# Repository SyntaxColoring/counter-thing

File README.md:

# Introduction

The Counter Thing is a hardware device with a button and numeric display. It currently counts days going up, and resets to 0 when you press the button.

I should run ~1 year on a CR2032 battery and keep time with a drift of <15 minutes/year.

I use a few as household reminders, like keeping track of how many days it's been since I've last vacuumed or watered my plants.

This repository holds everything for the project (electronics and software).

# File organization

[pcb/](./pcb/) has the KiCad project files for the latest version of the board. [pcb/fabrication_outputs/](./pcb/fabrication_outputs) has pre-exported Gerbers and such, ready to send to a fab. I used JLCPCB, but any of them will probably work.

[firmware/](./firmware/) has the STM32CubeIDE project files and source code for the firmware.

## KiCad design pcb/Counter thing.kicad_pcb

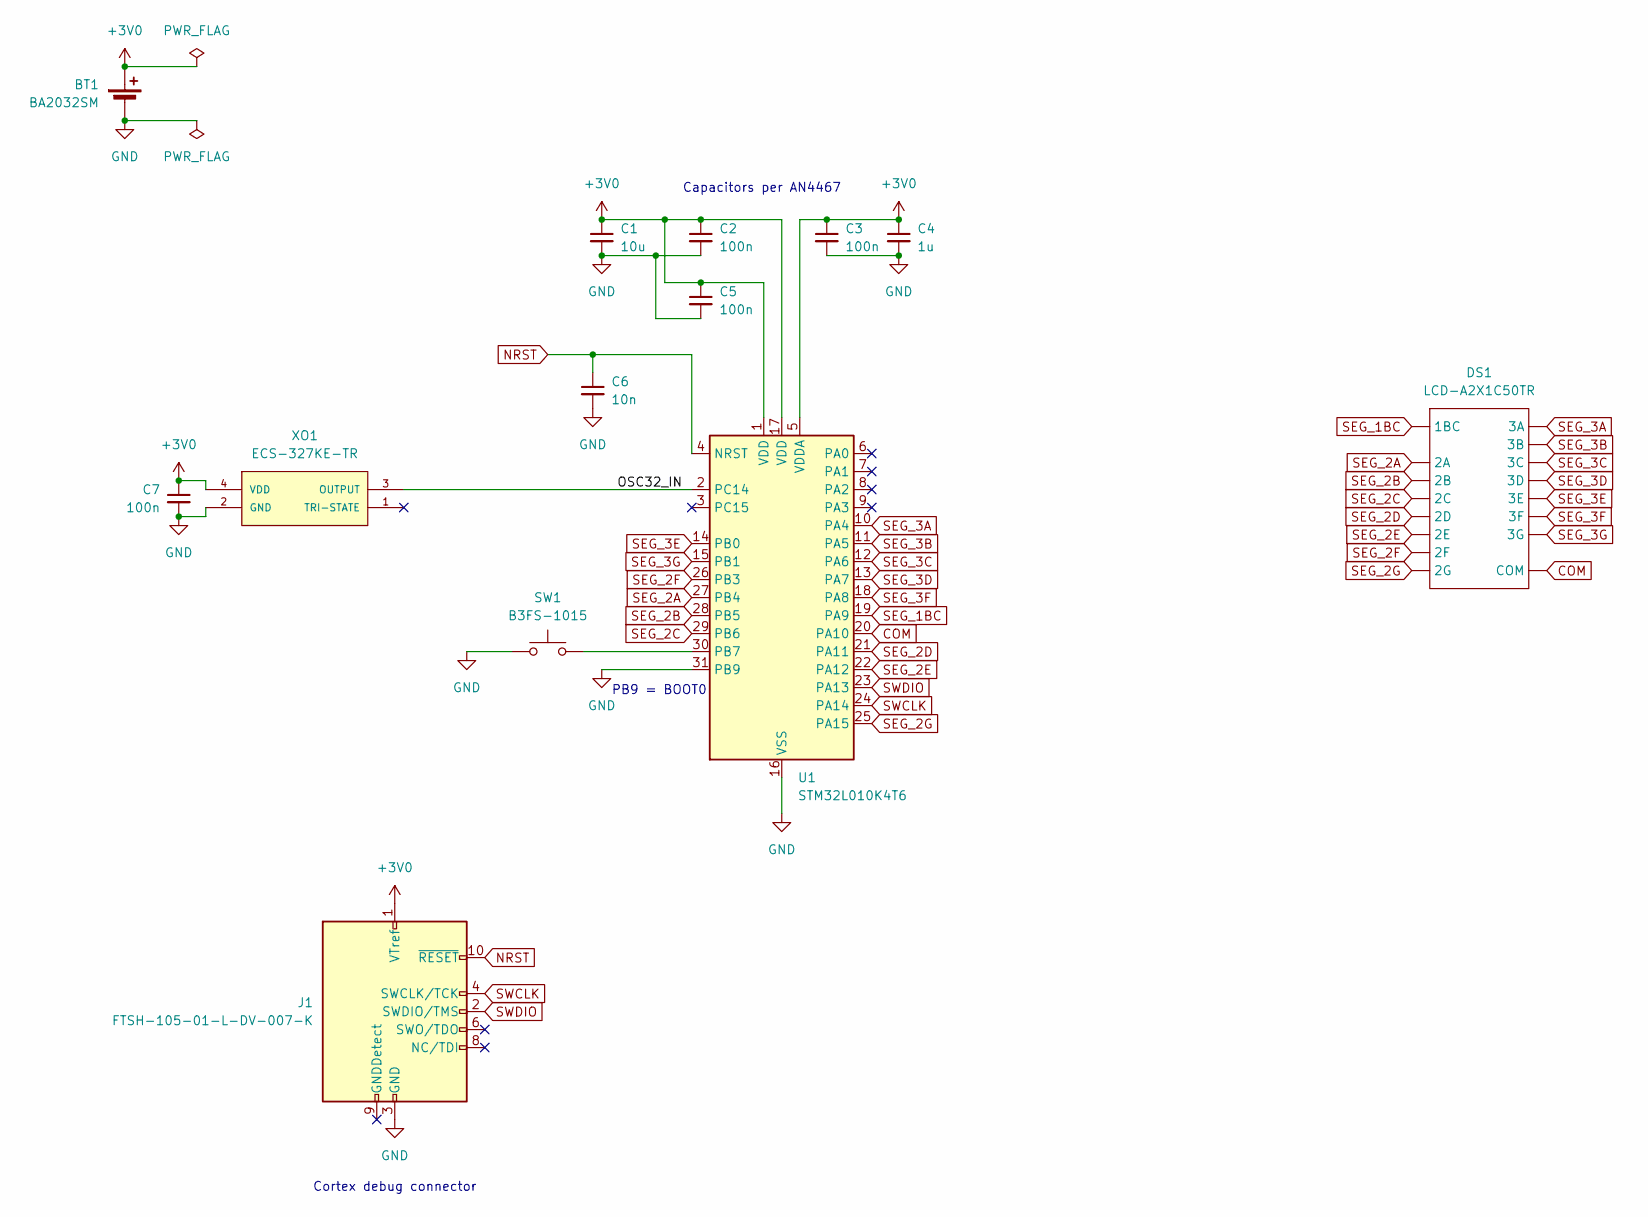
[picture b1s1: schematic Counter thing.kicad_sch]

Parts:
BT1: BA2032SM; MPN BA2032SM
C1: 10u; C_0805_2012Metric_Pad1.18x1.45mm_HandSolder; MPN C0805C106K8PAC7800
C2, C3, C5, C7: 100n; C_0805_2012Metric_Pad1.18x1.45mm_HandSolder; MPN C0805C104K5RAC7210
C4: 1u; C_0805_2012Metric_Pad1.18x1.45mm_HandSolder; MPN C0805C105K4RAC7800
C6: 10n; C_0805_2012Metric_Pad1.18x1.45mm_HandSolder; MPN C0805C103K1RAC7800
DS1: LCD-A2X1C50TR; MPN LCD-A2X1C50TR
J1: FTSH-105-01-L-DV-007-K; SAMTEC_FTSH-105-X-X-DV-007-P-X; MPN FTSH-105-01-L-DV-007-K
SW1: B3FS-1015; SW_SPST_Omron_B3FS-101xP; MPN B3FS-1015
U1: STM32L010K4T6; LQFP-32_7x7mm_P0.8mm; MPN STM32L010K4T6
XO1: ECS-327KE-TR; OSC_ECS-327KE-TR_HandSolder; MPN ECS-327KE-TR

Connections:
+3V0: BT1.1 (+), C1.1, C2.1, C3.1, C4.1, C5.1, C7.1, J1.1 (VTref), U1.1 (VDD), U1.5 (VDDA), U1.17 (VDD), XO1.4 (VDD)
/OSC32_IN: U1.2 (PC14), XO1.3 (OUTPUT)
COM: DS1.16 (COM), U1.20 (PA10)
GND: BT1.2 (-), C1.2, C2.2, C3.2, C4.2, C5.2, C6.2, C7.2, J1.3 (GND), J1.5 (GND), SW1.2, U1.16 (VSS), U1.31 (PB9), U1.32 (VSS), XO1.2 (GND)
NRST: C6.1, J1.10 (~RESET), U1.4 (NRST)
unnamed: SW1.1, U1.30 (PB7)
SEG_1BC: DS1.1 (1BC), U1.19 (PA9)
SEG_2A: DS1.11 (2A), U1.27 (PB4)
SEG_2B: DS1.10 (2B), U1.28 (PB5)
SEG_2C: DS1.9 (2C), U1.29 (PB6)
SEG_2D: DS1.15 (2D), U1.21 (PA11)
SEG_2E: DS1.14 (2E), U1.22 (PA12)
SEG_2F: DS1.12 (2F), U1.26 (PB3)
SEG_2G: DS1.13 (2G), U1.25 (PA15)
SEG_3A: DS1.8 (3A), U1.10 (PA4)
SEG_3B: DS1.7 (3B), U1.11 (PA5)
SEG_3C: DS1.6 (3C), U1.12 (PA6)
SEG_3D: DS1.5 (3D), U1.13 (PA7)
SEG_3E: DS1.4 (3E), U1.14 (PB0)
SEG_3F: DS1.2 (3F), U1.18 (PA8)
SEG_3G: DS1.3 (3G), U1.15 (PB1)
SWCLK: J1.4 (SWCLK/TCK), U1.24 (PA14)
SWDIO: J1.2 (SWDIO/TMS), U1.23 (PA13)

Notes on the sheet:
PB9 = BOOT0
Capacitors per AN4467
Cortex debug connector

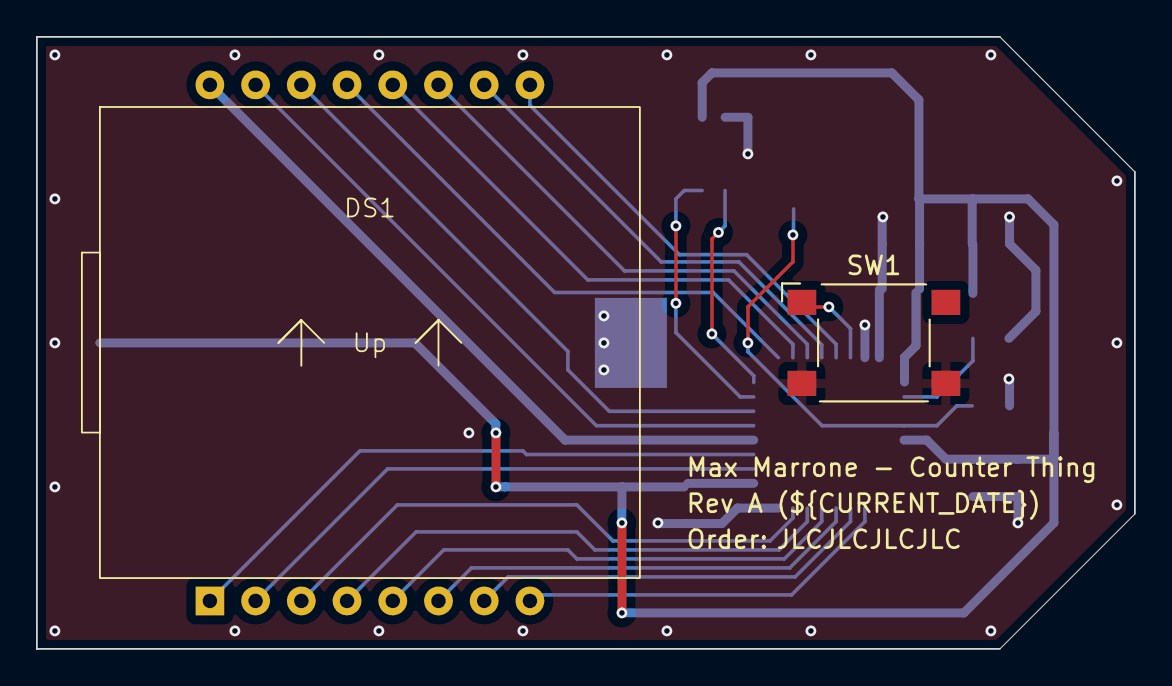
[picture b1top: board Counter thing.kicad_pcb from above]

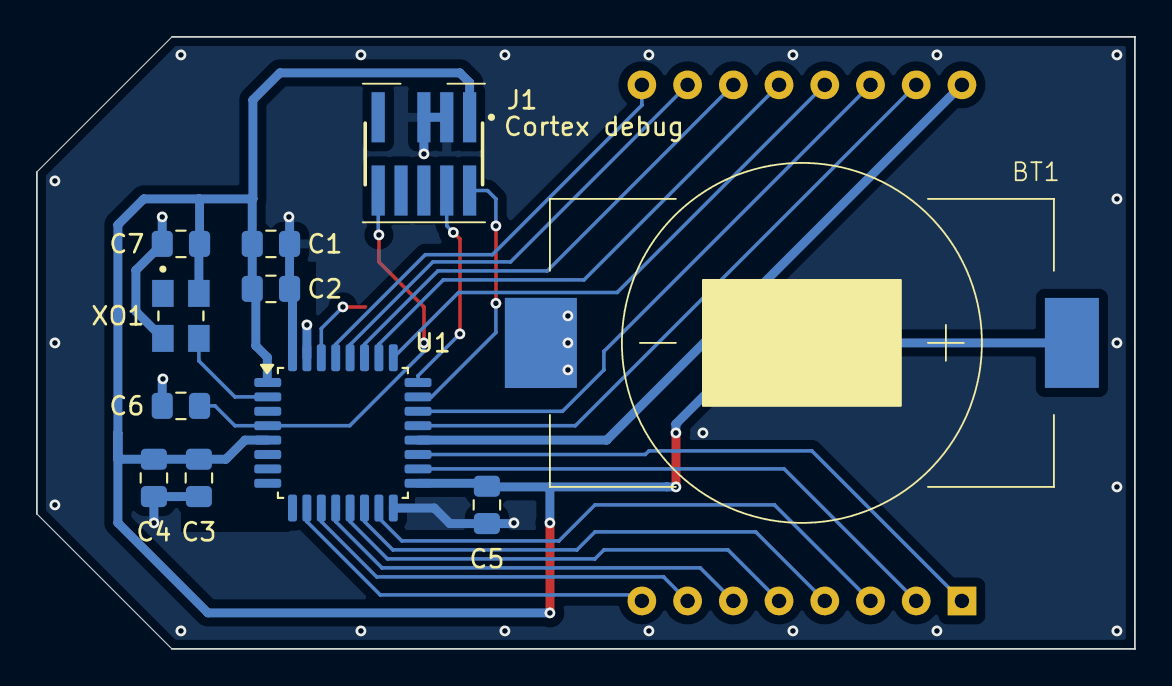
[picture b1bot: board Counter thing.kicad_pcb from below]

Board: 2 copper layers, 61.0 x 34.0 mm, 13 parts (11 on the bottom side), 23 nets.

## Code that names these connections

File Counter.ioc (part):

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Mcu.Name=STM32L010K4Tx
Mcu.Package=LQFP32
Mcu.UserName=STM32L010K4Tx
PA10.GPIOParameters=GPIO_Label
PA10.GPIO_Label=COM
PA10.Signal=GPIO_Output
PA11.GPIOParameters=GPIO_Label
PA11.GPIO_Label=SEG_2D
PA11.Signal=GPIO_Output
PA12.GPIOParameters=GPIO_Label
PA12.GPIO_Label=SEG_2E
PA12.Signal=GPIO_Output
PA13.Mode=Serial_Wire
PA13.Signal=SYS_SWDIO
PA14.Mode=Serial_Wire
PA14.Signal=SYS_SWCLK
PA15.GPIOParameters=GPIO_Label
PA15.GPIO_Label=SEG_2G
PA15.Signal=GPIO_Output
PA4.GPIOParameters=GPIO_Label
PA4.GPIO_Label=SEG_3A
PA4.Signal=GPIO_Output
PA5.GPIOParameters=GPIO_Label
PA5.GPIO_Label=SEG_3B
PA5.Signal=GPIO_Output
PA6.GPIOParameters=GPIO_Label
PA6.GPIO_Label=SEG_3C
PA6.Signal=GPIO_Output
PA7.GPIOParameters=GPIO_Label
PA7.GPIO_Label=SEG_3D
PA7.Signal=GPIO_Output
PA8.GPIOParameters=GPIO_Label
PA8.GPIO_Label=SEG_3F
PA8.Signal=GPIO_Output
PA9.GPIOParameters=GPIO_Label
PA9.GPIO_Label=SEG_1BC
PA9.Signal=GPIO_Output
PB0.GPIOParameters=GPIO_Label
PB0.GPIO_Label=SEG_3E
PB0.Signal=GPIO_Output
PB1.GPIOParameters=GPIO_Label
PB1.GPIO_Label=SEG_3G
PB1.Signal=GPIO_Output
PB3.GPIOParameters=GPIO_Label
PB3.GPIO_Label=SEG_2F
PB3.Signal=GPIO_Output
PB4.GPIOParameters=GPIO_Label
PB4.GPIO_Label=SEG_2A
PB4.Signal=GPIO_Output
PB5.GPIOParameters=GPIO_Label
PB5.GPIO_Label=SEG_2B
PB5.Signal=GPIO_Output
PB6.GPIOParameters=GPIO_Label
PB6.GPIO_Label=SEG_2C
PB6.Signal=GPIO_Output
PB7.GPIOParameters=GPIO_PuPd,GPIO_Label,GPIO_ModeDefaultEXTI
PB7.GPIO_Label=BUTTON
PB7.GPIO_ModeDefaultEXTI=GPIO_MODE_IT_RISING
PB7.GPIO_PuPd=GPIO_PULLUP
PB7.Signal=GPXTI7
PC14-OSC32_IN.Mode=LSE-External-Clock-Source
PC14-OSC32_IN.Signal=RCC_OSC32_IN
RCC.HSE_VALUE=8000000
RCC.SYSCLKFreq_VALUE=2097000
board=custom

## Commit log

2024-07-23 Initial commit. Count seconds up to 199.
2024-07-23 Make some stuff static.
2024-07-23 Use STOP mode and RTC auto-wakeup.
    This brings current consumption down from ~380 uA to ~33 uA.
2024-07-23 Add Release/ to gitignore.
2024-07-23 Clear count on button press.
2024-07-23 Use low-power regulator in stop mode.
    This brings us down to ~18 uA.
2024-07-23 Move generated peripheral init to separate files.
2024-07-23 Lock SWCLK and SWDIO pins.
2024-07-23 Count days instead of seconds.
2024-07-23 Fix modular arithmetic error.
2024-07-23 Move generated peripheral init back to main.c.
2024-07-25 EEPROM experiment
2024-07-27 Move display stuff to its own file.
2024-07-28 Move firmware into a firmware/ directory.
2024-07-28 Add PCB files.
2024-07-28 Ignore more KiCad files.
2024-07-28 Add readme.
2024-07-28 Update KiCad page titles.
2024-07-28 Add KiCad fabrication outputs.
2024-07-29 Remove KiCad project local settings from Git.
